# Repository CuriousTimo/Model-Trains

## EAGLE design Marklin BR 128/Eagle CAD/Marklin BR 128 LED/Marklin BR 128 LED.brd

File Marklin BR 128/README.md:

Files to Convert a Märklin BR 128 to 21MTC and update the LED lights
===================================

## Needed for conversion

<ul>
<li>1x New circuit board for 21MTC</li>
<li>2x New circuit board for the lighting</li>
<li>2x 3D printed spacers to prevent light leakage</li>
</ul>

## ESU LokPilot 5 Programming
<ul>
<li>F1: High beam in the direction of travel</li>
<li>F2: Reserved for cabin lighting</li>
<li>F3: Shunting (only the right headlight on both sides of the locomotive lights up)</li>
<li>F5: switch off the rear light (to pull a train at the rear)</li>
<li>F6: switch off the front light (to pull a train in front)</li>
</ul>

The lighting F5 and F6 works because the rear LEDs are on AUX 1 & AUX 2 and switched separately.

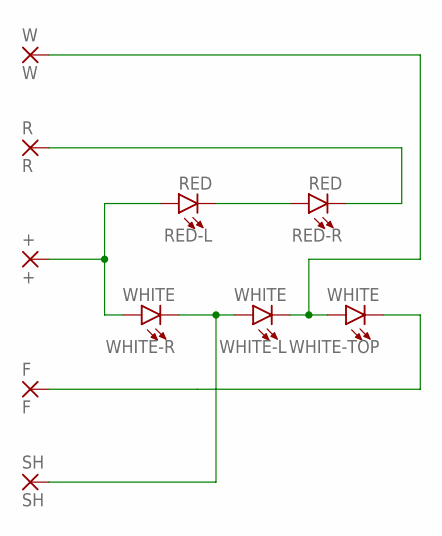
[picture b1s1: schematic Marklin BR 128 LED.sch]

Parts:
+: +; SMD1,27-2,54
F: F; SMD1,27-2,54
R: R; SMD1,27-2,54
RED-L: RED; LED-0603
RED-R: RED; LED-0603
SH: SH; SMD1,27-2,54
W: W; SMD1,27-2,54
WHITE-L: WHITE; LED-0603
WHITE-R: WHITE; LED-0603
WHITE-TOP: WHITE; LED-0603

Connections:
+: +.1, RED-L.A, WHITE-R.A
F: F.1, WHITE-TOP.C
unnamed: RED-L.C, RED-R.A
unnamed: W.1, WHITE-L.C, WHITE-TOP.A
R: R.1, RED-R.C
SH: SH.1, WHITE-L.A, WHITE-R.C

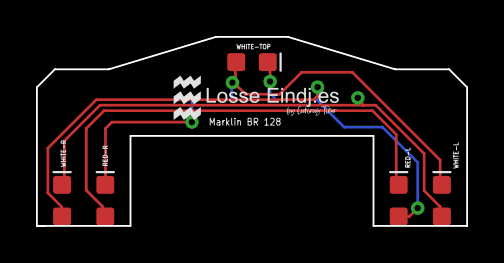
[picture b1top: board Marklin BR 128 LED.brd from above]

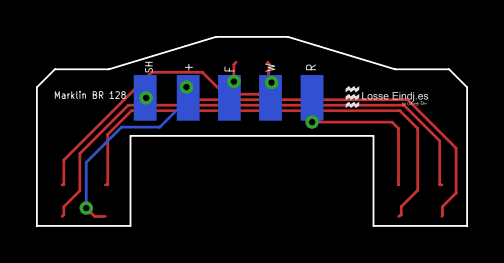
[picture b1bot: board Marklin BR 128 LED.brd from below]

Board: 2 copper layers, 23.9 x 10.5 mm, 10 parts (5 on the bottom side), 6 nets.

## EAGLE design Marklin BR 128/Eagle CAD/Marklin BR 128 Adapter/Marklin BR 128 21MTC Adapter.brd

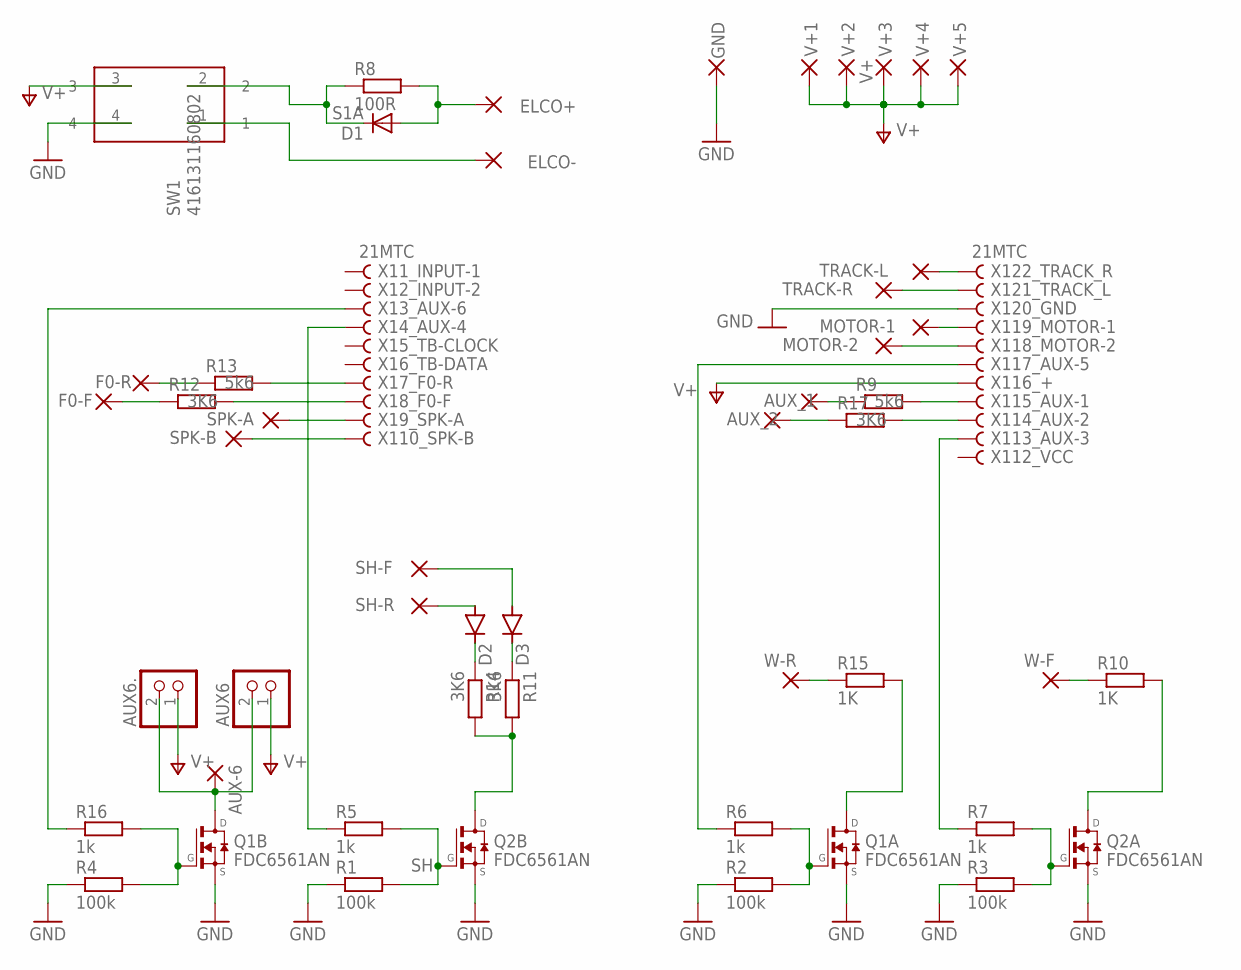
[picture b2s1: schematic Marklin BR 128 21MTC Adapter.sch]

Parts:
AUX6, AUX6.: JST_2PIN-THM-RA; JST-PH-2-THM-RA
AUX-6: SMD2; SMD1,27-2,54
AUX_1, AUX_2: SMD2; SMD1,27-2,54
D1: S1A; DO214AC
D2, D3: S1M; SMA
ELCO+: SMD2; SMD1,27-2,54
ELCO-: SMD2; SMD1,27-2,54
F0-F, F0-R: SMD2; SMD1,27-2,54
GND: SMD2; SMD1,27-2,54
MOTOR-1, MOTOR-2: SMD2; SMD1,27-2,54
Q1, Q2: FDC6561AN; SSOT-6
R1, R2, R3, R4: 100k; R0603
R5, R6, R7, R16: 1k; R0603
R8: 100R; R0603
R9, R13: 5k6; R0603
R10, R15: 1K; R0603
R11, R12, R14, R17: 3K6; R0603
SH-F: SH; SMD1,27-2,54
SH-R: AUX-2_(SH); SMD1,27-2,54
SPK-A: SMD2; SMD1,27-2,54
SPK-B: SMD2; SMD1,27-2,54
SW1: 416131160802
TRACK-L: SMD2; SMD1,27-2,54
TRACK-R: SMD2; SMD1,27-2,54
V+1, V+2, V+4, V+5: SMD2; SMD1,27-2,54
V+3: V+; SMD1,27-2,54
W-F: AUX-1_(W); SMD1,27-2,54
W-R: AUX-1_(W); SMD1,27-2,54
X1: 21MTC

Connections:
ELCO+: D1.A, ELCO+.1, R8.2
ELCO-: ELCO-.1, SW1.1
GND: GND.1, Q1.2 (S), Q1.5 (S), Q2.2 (S), Q2.5 (S), R1.1, R2.1, R3.1, R4.1, SW1.4, X1.20
MOTOR2: MOTOR-2.1, X1.18
MOTOR-1: MOTOR-1.1, X1.19
unnamed: R7.1, X1.13
unnamed: Q2.1 (G), R3.2, R7.2
unnamed: R5.1, X1.4
unnamed: Q2.3 (G), R1.2, R5.2
unnamed: AUX6.2 (1), AUX6..2 (1), AUX-6.1, Q1.4 (D)
unnamed: Q1.1 (G), R2.2, R6.2
unnamed: R6.1, X1.17
unnamed: R16.1, X1.3
unnamed: D1.C, R8.1, SW1.2
unnamed: Q1.3 (G), R4.2, R16.2
unnamed: D2.A, SH-R.1
unnamed: Q1.6 (D), R15.2
unnamed: R10.1, W-F.1
unnamed: D3.A, SH-F.1
unnamed: R13.2, X1.7
unnamed: R12.2, X1.8
unnamed: SPK-A.1, X1.9
unnamed: SPK-B.1, X1.10
unnamed: Q2.4 (D), R11.2, R14.2
unnamed: D2.C, R14.1
unnamed: R15.1, W-R.1
unnamed: D3.C, R11.1
unnamed: R9.2, X1.15
unnamed: R17.2, X1.14
unnamed: AUX_1.1, R9.1
unnamed: AUX_2.1, R17.1
unnamed: Q2.6 (D), R10.2
unnamed: F0-F.1, R12.1
unnamed: F0-R.1, R13.1
TRACK-L: TRACK-L.1, X1.22
TRACK-R: TRACK-R.1, X1.21
V+: AUX6.1 (2), AUX6..1 (2), SW1.3, V+1.1, V+2.1, V+3.1, V+4.1, V+5.1, X1.16

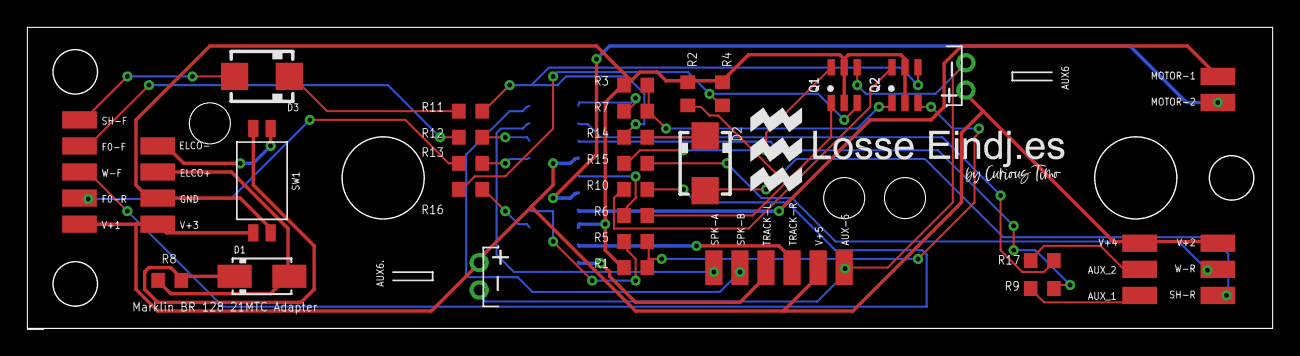
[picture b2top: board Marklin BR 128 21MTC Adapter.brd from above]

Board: 2 copper layers, 90.9 x 21.9 mm, 49 parts (1 on the bottom side), 37 nets.

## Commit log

2021-04-25 EAGLE added
    EAGLE added
2021-04-25 DS_Store remove
2021-04-26 Rolling Test Stand

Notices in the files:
parts and their libraries:
Wurth_Elektronik_Electromechanic_Switchs: Copyright: Würth Elektronik
SparkFun-LED: Licensing: Creative Commons ShareAlike 4.0 International - https://creativecommons.org/licenses/by-sa/4.0
